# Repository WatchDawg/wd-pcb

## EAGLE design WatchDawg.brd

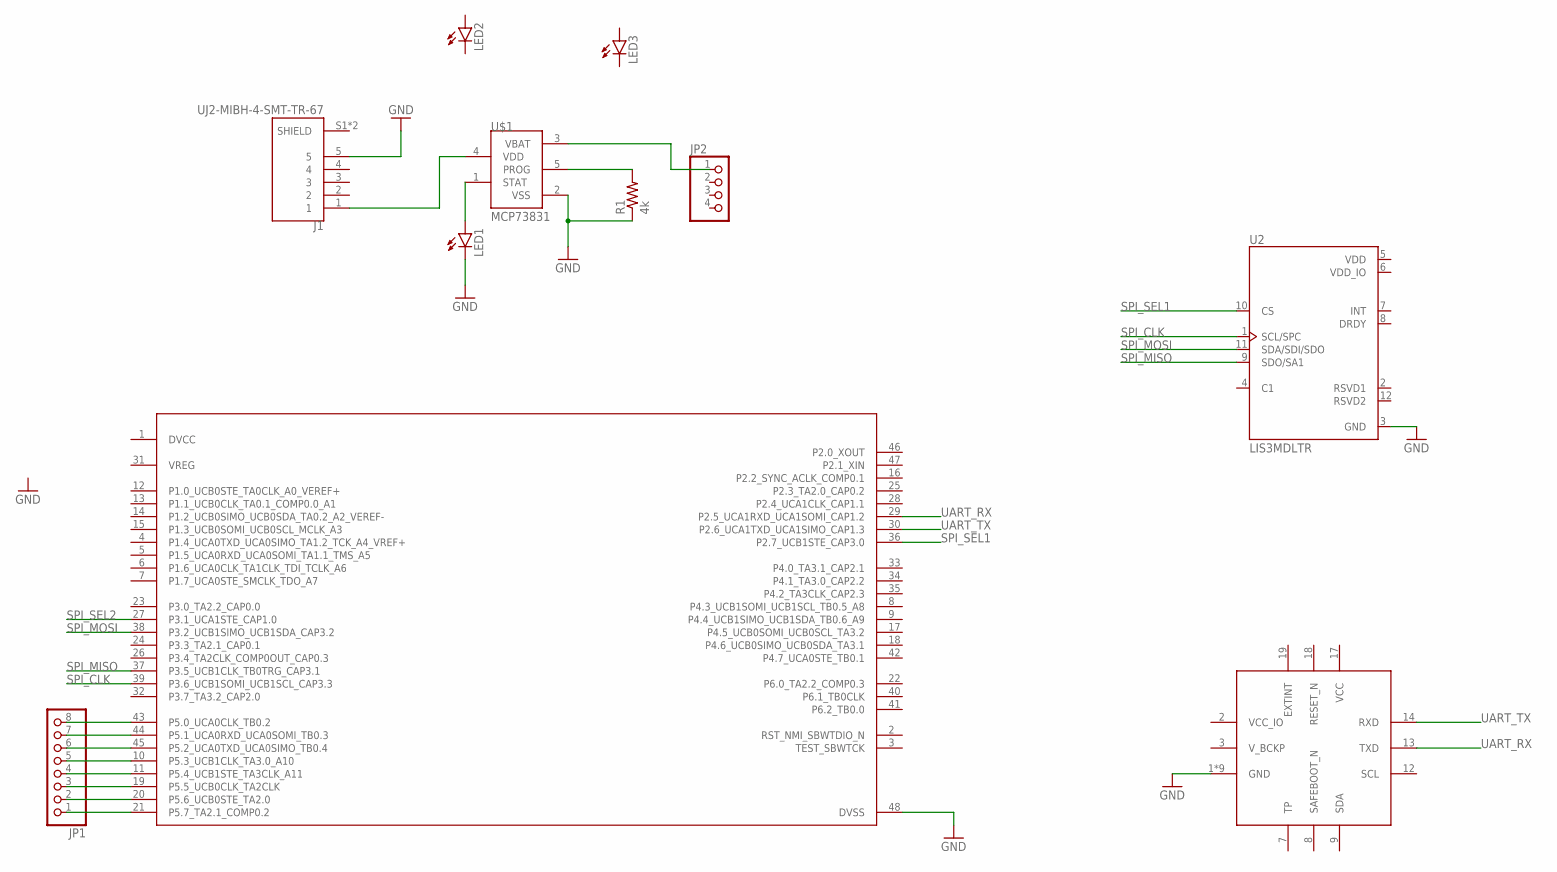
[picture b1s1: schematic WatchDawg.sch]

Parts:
IC1: SAM-M8Q
J1: UJ2-MIBH-4-SMT-TR-67; CUI_UJ2-MIBH-4-SMT-TR-67
JP1: PINHD-1X8; 1X08
JP2: PINHD-1X4; 1X04
LED1, LED2, LED3: LEDCHIPLED_0603; CHIPLED_0603
MSP430: Value; PT0048A_N
R1: 4k; R0603
U2: LIS3MDLTR; XDCR_LIS3MDLTR
U$1: MCP73831; SOT23-5L

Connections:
DVCC: MSP430.1 (DVCC)
GND: IC1.1 (GND), IC1.4 (GND), IC1.5 (GND), IC1.6 (GND), IC1.10 (GND), IC1.11 (GND), IC1.15 (GND), IC1.16 (GND), IC1.20 (GND), J1.5, LED1.C, MSP430.48 (DVSS), R1.1, U2.3 (GND), U$1.2 (VSS)
unnamed: JP1.8, MSP430.43 (P5.0_UCA0CLK_TB0.2)
unnamed: JP1.7, MSP430.44 (P5.1_UCA0RXD_UCA0SOMI_TB0.3)
unnamed: JP1.6, MSP430.45 (P5.2_UCA0TXD_UCA0SIMO_TB0.4)
unnamed: JP1.5, MSP430.10 (P5.3_UCB1CLK_TA3.0_A10)
unnamed: JP1.4, MSP430.11 (P5.4_UCB1STE_TA3CLK_A11)
unnamed: JP1.3, MSP430.19 (P5.5_UCB0CLK_TA2CLK)
unnamed: JP1.2, MSP430.20 (P5.6_UCB0STE_TA2.0)
unnamed: JP1.1, MSP430.21 (P5.7_TA2.1_COMP0.2)
unnamed: LED1.A, U$1.1 (STAT)
unnamed: R1.2, U$1.5 (PROG)
unnamed: JP2.1, U$1.3 (VBAT)
unnamed: J1.1, U$1.4 (VDD)
SPI_CLK: MSP430.39 (P3.6_UCB1SOMI_UCB1SCL_CAP3.3), U2.1 (SCL/SPC)
SPI_MISO: MSP430.37 (P3.5_UCB1CLK_TB0TRG_CAP3.1), U2.9 (SDO/SA1)
SPI_MOSI: MSP430.38 (P3.2_UCB1SIMO_UCB1SDA_CAP3.2), U2.11 (SDA/SDI/SDO)
SPI_SEL1: MSP430.36 (P2.7_UCB1STE_CAP3.0), U2.10 (CS)
SPI_SEL2: MSP430.27 (P3.1_UCA1STE_CAP1.0)
UART_RX: IC1.13 (TXD), MSP430.29 (P2.5_UCA1RXD_UCA1SOMI_CAP1.2)
UART_TX: IC1.14 (RXD), MSP430.30 (P2.6_UCA1TXD_UCA1SIMO_CAP1.3)
VDD: U2.5 (VDD)
VDD_IO: U2.6 (VDD_IO)
VREG: MSP430.31 (VREG)

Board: 2 copper layers, 11 parts (0 on the bottom side), 19 nets, no tracks yet.

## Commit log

2019-10-24 Migrate to Altium, MCU in CAD
2019-10-24 Added magnetometer schematic
2019-10-25 added charger project
2019-10-25 adds LDO and drill holes to PCB
2019-10-26 charger pcb v2 done
2019-10-28 updates structure of WatchDawg project
2019-10-29 cleans up folder structure, adds git ignore
2019-10-29 adds most required components, buttons to come later
2019-10-29 adds saved project file
2019-10-31 ratsnest created
2019-10-31 Finished routing PCB
2019-11-01 Applied Mark's suggestions, ready to print V1
2019-11-01 Generated Gerbers
2019-11-16 updates PCB
2019-11-16 added pull up resistors to I2C, updates epaper pinouts and provides more GPIO debug pins, GPS TX and RX pinouts, routes charger output to ADC pin
2019-11-17 Added resistors for battery voltage sensor
2019-11-18 PCB 4 Layer Ordered
2019-11-18 Finish 2 layer board
2019-11-18 Generated PDF
2019-11-25 adds screenshot of top layer
